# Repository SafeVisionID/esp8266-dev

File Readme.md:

This contains [ESP8266EX](https://www.espressif.com/en/products/hardware/esp8266ex/overview) development as an alternative to [latest official](https://github.com/SafeVisionID/esp-latestcode) development.
This hopes can be scale-up as implementation/requirement applied.

Based on [ESP-Open-SDK](https://github.com/pfalcon/esp-open-sdk) which in turn based on Espressif's [Non-OS SDK](https://github.com/espressif/ESP8266_NONOS_SDK)

To install required SDK:
- Arch-Linux, available at [AUR](https://aur.archlinux.org/packages/esp-open-sdk-git/)
- Others, follow this [guide](https://github.com/pfalcon/esp-open-sdk/blob/master/README.md)

-----------------------------------------------------------------------

Fearture and To-Do list:
- [x] Basic LED Blink
- [x] UART Boot Info
- [x] UART Shell and Response/Callback
- [x] GPIO Interrupt (using Polling)
- [x] Basic HTTP Server
	- [x] Basic HTML Response
	- [x] Serial Out Response
	- [x] Reset Request
	- [x] R/W Integer/String in Flash
	- [x] Receive Serial Request
- [x] Wifi Station mode
	- [x] Config Password
	- [x] Config SSID
- [x] Wifi SoftAP mode
	- [x] Default IP, SSID, and Password
	- [x] Config Station SSID and Password
	- [x] Config Device ID
- [x] Switch Station and SoftAP
	- [x] WiFi Status Indicator (LED GPIO2)
	- [x] by HTTP Request
	- [x] by GPIO pin
- [ ] Sensor Interface
	- [x] Magnet Switch
	- [x] PIR (Cont-Trigger and 3v3)
	- [ ] Server Checking
	- [ ] Server Report
- [ ] Sleep and WakeUp
	- [x] by Sleep Time-Out
	- [ ] by Sensor Trigger
- [ ] Power Manager Circuit
	- [ ] Battery (LiPO)
	- [ ] Regulator (AMS1117)
- [ ] PCB
	- [x] Main
	- [ ] Battery Regulator
- [ ] Additional
	- [x] ADC Interface
	
-----------------------------------------------------------------------

Copyright (C) Wira ST MT

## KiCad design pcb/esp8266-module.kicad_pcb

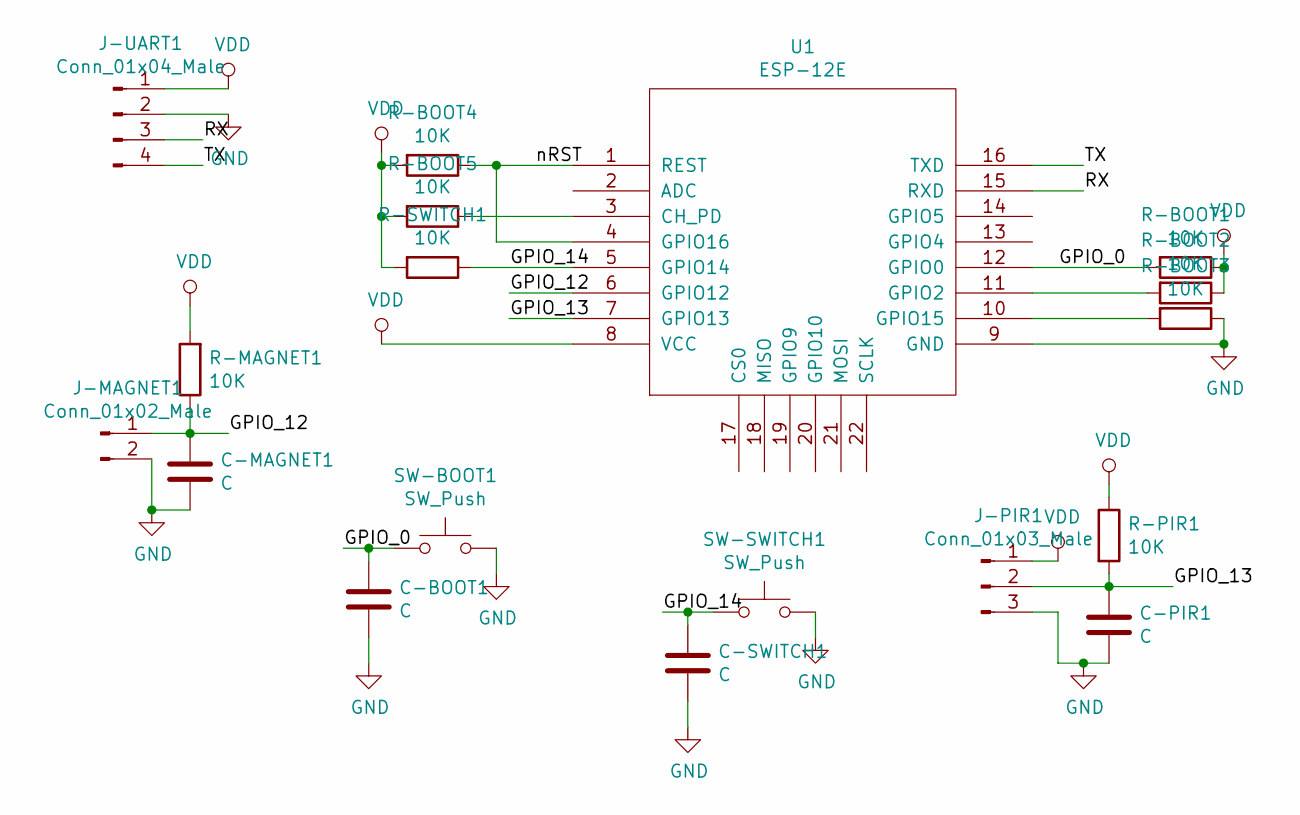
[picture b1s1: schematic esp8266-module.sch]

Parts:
C-BOOT1: C; C_0805_2012Metric
C-MAGNET1: C; C_0805_2012Metric
C-PIR1: C; C_0805_2012Metric
C-SWITCH1: C; C_0805_2012Metric
J-MAGNET1: Conn_01x02_Male; solderpads_1x2
J-PIR1: Conn_01x03_Male; solderpads_1x3
J-UART1: Conn_01x04_Male; solderpads_1x4
R-BOOT1, R-BOOT2, R-BOOT3, R-BOOT4, R-BOOT5: 10K; R_0805_2012Metric
R-MAGNET1: 10K; R_0805_2012Metric
R-PIR1: 10K; R_0805_2012Metric
R-SWITCH1: 10K; R_0805_2012Metric
SW-BOOT1: SW_Push; SW_SPST_B3U-1000P-B
SW-SWITCH1: SW_Push; SW_SPST_B3U-1000P-B
U1: ESP-12E

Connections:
/GPIO_0: C-BOOT1.1, R-BOOT1.2, SW-BOOT1.1, U1.12 (GPIO0)
/GPIO_12: C-MAGNET1.1, J-MAGNET1.1, R-MAGNET1.1, U1.6 (GPIO12)
/GPIO_13: C-PIR1.1, J-PIR1.2, R-PIR1.2, U1.7 (GPIO13)
/GPIO_14: C-SWITCH1.1, R-SWITCH1.1, SW-SWITCH1.1, U1.5 (GPIO14)
/RX: J-UART1.3, U1.15 (RXD)
/TX: J-UART1.4, U1.16 (TXD)
/nRST: R-BOOT4.1, U1.1 (REST), U1.4 (GPIO16)
GND: C-BOOT1.2, C-MAGNET1.2, C-PIR1.2, C-SWITCH1.2, J-MAGNET1.2, J-PIR1.3, J-UART1.2, R-BOOT3.1, SW-BOOT1.2, SW-SWITCH1.2, U1.9 (GND)
unnamed: R-BOOT2.2, U1.11 (GPIO2)
unnamed: R-BOOT3.2, U1.10 (GPIO15)
unnamed: R-BOOT5.1, U1.3 (CH_PD)
VDD: J-PIR1.1, J-UART1.1, R-BOOT1.1, R-BOOT2.1, R-BOOT4.2, R-BOOT5.2, R-MAGNET1.2, R-PIR1.1, R-SWITCH1.2, U1.8 (VCC)

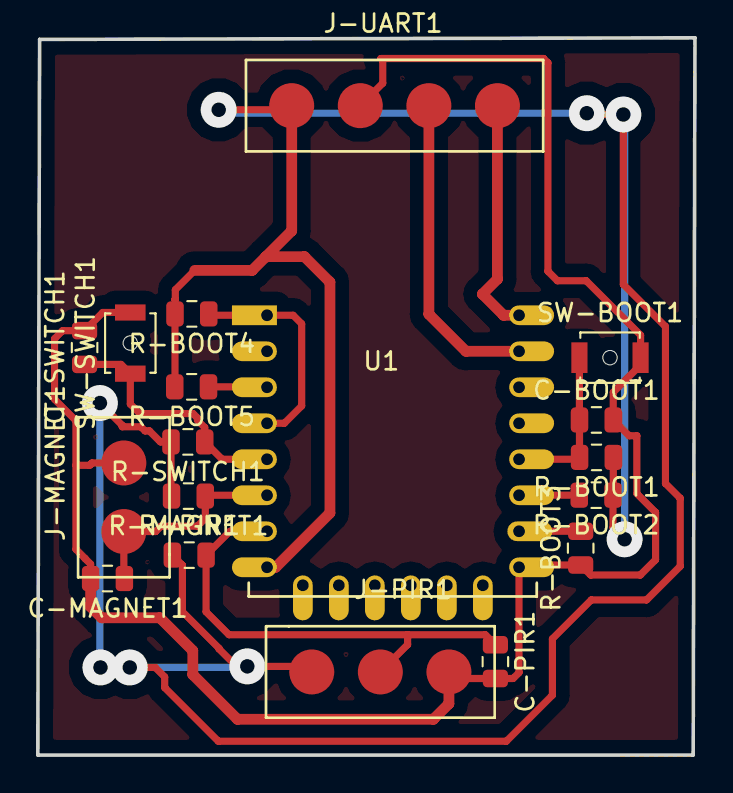
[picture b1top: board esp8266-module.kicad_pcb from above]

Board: 2 copper layers, 36.5 x 39.9 mm, 18 parts (0 on the bottom side), 12 nets.

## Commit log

2019-10-08 initial README
2019-10-08 common Makefile
2019-10-08 initial user code
2019-10-08 blinky
2019-10-08 add qt creator project
2019-10-08 add driver folder
2019-10-08 no need driver
2019-10-08 add some system info
2019-10-08 add build date/time
2019-10-09 working examples
2019-10-09 trim function
2019-10-09 UART Receive Callback OK
2019-10-10 update to-do list
2019-10-10 http request and wifi station mode
2019-10-10 wifi soft ap
2019-10-10 Wifi SoftAP working
2019-10-10 Update Redame
2019-10-10 Set on SoftAP then run on Station
2019-10-11 basic flash R/W
2019-10-11 RW flash on 1 variables
2019-10-11 RW Integer/String in Flash
2019-10-11 led blink on own class
2019-10-11 Station Mode Connect LED
2019-10-11 ignore some useless generated files
2019-10-11 LED GPIO2 WiFi indicator
2019-10-13 wifi switch on own function
2019-10-13 user_config.h not really used now
2019-10-13 GPIO0 Interrupt (non-polling) still not working
2019-10-14 interrupt gpio (untested)
2019-10-14 restructuring
2019-10-14 GPIO Interrupt (using Polling)
2019-10-14 GPIO Interrupt still not triggered (whyyyyyyyyyy????)
2019-10-15 Adjust IP using definition
2019-10-15 following availabel Android setup
2019-10-16 ssid and pass follow app
2019-10-16 reconfig blinky led
2019-10-16 reprogram follow app
2019-10-16 LED WiFi Station Unconnected
2019-10-16 wifi station led blink
2019-10-24 update info
2019-10-24 update some name and gpio_init called once only
2019-10-24 gpio interrupt running without polling
    previous mistake: gpio_init() was called after interrupt init
2019-10-25 back Interrupt by Polling
2019-10-25 esp8266 kicad lib
2019-10-25 schematic PNG
2019-10-25 PCB first
2019-10-25 re-map I/O
2019-10-26 I/O using polling interrupt
2019-10-27 ADC and timed Deep-Sleep
2019-10-27 JSON output and sensor last checking
2019-10-28 Add dcoumentation
2019-10-28 Doumentation Complete
2019-10-28 Completing Transfer Copyright
2019-11-02 Flash read get code-9 exception
2019-11-02 error seems only when building JSON
2019-11-02 config saved on flash in one string
2019-11-02 Flash configs in one string
2019-11-08 add check and emptying string
2019-11-08 wifi softAP set ssid by devs_id
2019-11-10 flash downloader
2019-11-10 script for simplify flashing
2019-11-10 add UART set device ID routine
2019-11-11 flash memory string management drive me crazy!!!
2019-11-11 why??????
2019-11-11 Next on HW: GUI to flash and set DeviceID
2019-11-12 start new tools
2019-11-12 new pyqt tools
2019-11-12 GUI Helper
2019-11-12 Interface and some bug fixes
2019-11-12 add more bug to fix later
2019-11-17 prepare for http client
2019-11-17 DNS resolver
2019-11-17 http client
2019-11-17 spesific GET request
2019-11-17 http client test
2019-11-18 Both GET and POST accessible
2019-11-18 add doxygen documentation
2020-01-15 http post request example
2020-01-15 post test
2020-01-16 start working on new web api
2020-01-16 got DNS pending
2020-01-16 DNS error
2020-01-16 DNS Pending anjiiing
2020-01-16 next:JSON/HTTP parser (DNS resolver crappy)
2020-01-16 DNS resolver error
2020-01-18 DNS resolver works
2020-01-18 simplify debug output
2020-01-18 HTTP-JSON parser
2020-02-19 continue on sensor create
2020-02-19 ignore build folder and PCB model
2020-02-20 confused with Server API itself
2020-03-09 update API
2020-03-09 configuring wifi station without stop
2020-03-11 prepare to implement address forwarding
2020-03-11 reset JSON receiver
2020-03-11 pending on URL redirect follow
2020-03-12 First development of PCB
2020-05-15 client NULL fail-safe
2021-02-21 new PCB
